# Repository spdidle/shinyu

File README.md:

# A-Side 🎼

## What is this?

A-Side is a cassette tape inspired hub to connect full size SD cards among other things to my laptop. I own several cameras but it's not convenient at all to find my dongle and connect it. So why not use a cute form to easily see your pictures!

## Why did I make this?

I love cassette tapes and cameras. That's it!

Loving cameras mean that every time I need to view my photos, upload my photos, anything to do with my photos, it's such a hassle! Grabbing my SD card reader, then my hard drive, sometimes another dongle... Anyways, it's just way too much work. So I decided to make my own SD card dongle-esque thing, with 2 USB-A ports to facilitate any connecting of hard drives, and 2 SD card slots to maximize the photo goodness. When I don't need to fiddle with photos, it can also act as a normal USB hub, allowing me to plug in keyboard or mice into my laptop.

## Features

- **2 USB-A ports** for portable hard drives, keyboards, or mice
- **2 Full-Size SD Card slots** for photos!
- **USB-C port** because nowadays, everything seems to be USB-C...

## How does it work?

Very self explanitory! Grab your favourite USB-C to USB-C cable, plug one end into your computer, the other into the hub, and voila! You are now able to plug whatever you want into this cute little cassette tape.

## Design

Designed in KiCad, schematic and board files are in this repo:

Case was designed (+ rendered) in Fusion360:

## BOM (Bill Of Materials)
|Designator                                           |Component Name / Description  |Package     |Value / Spec            |Qty|Unit Price (USD)|Total (USD)|Primary Supplier|Part Number / Source Link                                                                                                                                                                                              |
|-----------------------------------------------------|------------------------------|------------|------------------------|---|----------------|-----------|----------------|-----------------------------------------------------------------------------------------------------------------------------------------------------------------------------------------------------------------------|
|C1, C2                                               |Multilayer Ceramic Capacitor  |0805        |22pF                    |2  |0.4600          |$0.92      |LCSC            |https://www.lcsc.com/product-detail/C1804.html?s_z=n_q_CL21C220JBANNNC&lcsc_vid=FVBdVAJfRgcKUwcCQlVdBFQETlgIUlMAFFFcVAYEEVgxVlNeRlRXVVxWQVFdXzsOAxUeFF5JWBYZEEoKFBINSQcJGk4eFQsCAgIaSgADAwAHC0slQFVcU1NVTk8GEwkK       |
|C3                                                   |Multilayer Ceramic Capacitor  |0805        |1uF                     |1  |0.9400          |$0.94      |LCSC            |https://www.lcsc.com/product-detail/C28323.html?s_z=s_p_CL21B105KBFNNNE&lcsc_vid=FVBdVAJfRgcKUwcCQlVdBFQETlgIUlMAFFFcVAYEEVgxVlNeRlRXVVxQQVlbVjsOAxUeFF5JWBYZEEoKFBINSQcJGk4dAgUUFAk%3D                                |
|C10                                                  |Multilayer Ceramic Capacitor  |0805        |4.7uF                   |1  |0.4300          |$0.43      |LCSC            |https://www.lcsc.com/product-detail/C1779.html?s_z=s_p_CL21A475KAQNNNE&lcsc_vid=FVBdVAJfRgcKUwcCQlVdBFQETlgIUlMAFFFcVAYEEVgxVlNeRlRXVFVRT1lXUDsOAxUeFF5JWBYZEEoKFBINSQcJGk4dAgUUFAk%3D                                 |
|C11,C12,C13,C14,C15,C16,C17,C19,C20,C4,C5,C6,C7,C8,C9|Multilayer Ceramic Capacitor  |0805        |100nF                   |15 |0.0687          |$1.03      |LCSC            |https://www.lcsc.com/product-detail/C49678.html?s_z=n_q_CC0805KRX7R9BB104&lcsc_vid=FVBdVAJfRgcKUwcCQlVdBFQETlgIUlMAFFFcVAYEEVgxVlNeRlRXVFdQT1ZaUzsOAxUeFF5JWBYZEEoKFBINSQcJGk4eFQsCAgIaSgADAwAHC0slRlZZXkoOAwwC        |
|R1, R2, R5, R6                                       |Thick Film Chip Resistor      |0805        |100 kΩ                  |4  |0.0825          |$0.33      |LCSC            |https://www.lcsc.com/product-detail/C149504.html?s_z=s_p_0805W8F1003T5E&lcsc_vid=FVBdVAJfRgcKUwcCQlVdBFQETlgIUlMAFFFcVAYEEVgxVlNeRlRXVFFVT1deXjsOAxUeFF5JWBYZEEoKFBINSQcJGk4dAgUUFAk%3D                                |
|R4                                                   |Thick Film Chip Resistor      |0805        |680 Ω                   |1  |0.2200          |$0.22      |LCSC            |https://www.lcsc.com/product-detail/C17798.html?s_z=n_q_0805W8F6800T5E&lcsc_vid=FVBdVAJfRgcKUwcCQlVdBFQETlgIUlMAFFFcVAYEEVgxVlNeRlRXVFJVQ1BWVTsOAxUeFF5JWBYZEEoKFBINSQcJGk4eFQsCAgIaSgADAwAHC0slRlZZXlxIHxUDCw%3D%3D   |
|R7, R8                                               |Thick Film Chip Resistor      |0805        |330 Ω                   |2  |0.1400          |$0.28      |LCSC            |https://www.lcsc.com/product-detail/C17630.html?s_z=s_p_0805W8F3300T5E&lcsc_vid=FVBdVAJfRgcKUwcCQlVdBFQETlgIUlMAFFFcVAYEEVgxVlNeRlRXVFJeQlZXVjsOAxUeFF5JWBYZEEoKFBINSQcJGk4dAgUUFAk%3D                                 |
|R10, R23                                             |Thick Film Chip Resistor      |0805        |5.1 kΩ                  |2  |0.1400          |$0.28      |LCSC            |https://www.lcsc.com/product-detail/C27834.html?s_z=n_q_0805W8F5101T5E&lcsc_vid=FVBdVAJfRgcKUwcCQlVdBFQETlgIUlMAFFFcVAYEEVgxVlNeRlRXVFNXT1FeUDsOAxUeFF5JWBYZEEoKFBINSQcJGk4eFQsCAgIaSgADAwAHC0slRlZYVFRIHxUDCw%3D%3D   |
|R11-R20                                              |Thick Film Chip Resistor      |0805        |10 kΩ                   |14 |0.0250          |$0.35      |LCSC            |https://www.lcsc.com/product-detail/C17414.html?s_z=s_p_0805W8F1002T5E&lcsc_vid=FVBdVAJfRgcKUwcCQlVdBFQETlgIUlMAFFFcVAYEEVgxVlNeRlRXVFNfRFlXUjsOAxUeFF5JWBYZEEoKFBINSQcJGk4dAgUUFAk%3D                                 |
|D1, D2                                               |Surface Mount Indicator LED   |0805        |Standard Red/Green      |2  |0.3350          |$0.67      |LCSC            |https://www.lcsc.com/product-detail/C84256.html?s_z=s_p_NCD0805R1                                                                                                                                                      |
|SW1                                                  |SMT Tactile Push Button       |3.9x2.9mm   |1.6N / 2.0mm Height     |1  |2.2100          |$2.21      |LCSC            |https://www.lcsc.com/product-detail/C495942.html?s_z=n_q_MPTFP2-V-T%252FR&lcsc_vid=FVBdVAJfRgcKUwcCQlVdBFQETlgIUlMAFFFcVAYEEVgxVlNeRlRXVFxeRlRbUjsOAxUeFF5JWBYZEEoKFBINSQcJGk4eFQsCAgIaSgADAwAHC0slT1VcUlJIHxUDCw%3D%3D|
|CARD1, CARD2                                         |Hinged MicroSD Card Slot      |SMT         |SD-106M Hinged          |2  |0.5200          |$1.04      |LCSC            |https://www.lcsc.com/product-detail/C266603.html?s_z=s_p_SD-106M&lcsc_vid=FVBdVAJfRgcKUwcCQlVdBFQETlgIUlMAFFFcVAYEEVgxVlNeRlRXVF1VQFZXVDsOAxUeFF5JWBYZEEoKFBINSQcJGk4dAgUUFAk%3D                                       |
|GL850G                                               |USB 2.0 Hub Controller IC     |SSOP-28     |GL850G-HHY22            |1  |0.5500          |$0.55      |LCSC            |https://www.lcsc.com/product-detail/C136617.html?s_z=n_q_GL850G-HHY22&lcsc_vid=FVBdVAJfRgcKUwcCQlVdBFQETlgIUlMAFFFcVAYEEVgxVlNeRlRXVF1eTllbXzsOAxUeFF5JWBYZEEoKFBINSQcJGk4eFQsCAgIaSgADAwAHC0slRVdYUVRVWQkaCgg%3D      |
|IC3, IC4                                             |USB SD Card Reader Controller |SOP-16      |GL823K-HCY04            |2  |0.4550          |$0.91      |LCSC            |https://www.lcsc.com/product-detail/C284879.html?s_z=n_q_GL823K-HCY04&lcsc_vid=FVBdVAJfRgcKUwcCQlVdBFQETlgIUlMAFFFcVAYEEVgxVlNeRlRXU1RSR1JZVzsOAxUeFF5JWBYZEEoKFBINSQcJGk4NBhADEA4cHktfQ1hADxALGw%3D%3D                |
|U1, U2                                               |TVS Diode ESD Protection Array|SOT-23-6    |SRV05-4 (Low Cap)       |2  |0.2550          |$0.51      |LCSC            |https://www.lcsc.com/product-detail/C2836319.html?s_z=n_q_x_SRV05-4&lcsc_vid=FVBdVAJfRgcKUwcCQlVdBFQETlgIUlMAFFFcVAYEEVgxVlNeRlRXU1RRRFlfVTsOAxUeFF5JWBYZEEoKFBINSQcJGk4NBhADEA4cHktfQ1hADxALGw%3D%3D                  |
|USB1, USB2                                           |USB Type-A Receptacle         |Through-Hole|Right Angle / 90° Female|2  |0.2450          |$0.49      |LCSC            |https://www.lcsc.com/product-detail/C456018.html?s_z=n_q_p_AF%252090%2520WJDG&lcsc_vid=FVBdVAJfRgcKUwcCQlVdBFQETlgIUlMAFFFcVAYEEVgxVlNeRlRXU1VURlNYUDsOAxUeFF5JWBYZEEoKFBINSQcJGk4eFQsCAgIaSgADAwAHC0slRVldUVdXTk8GEwkK|
|USB3                                                 |USB Type-C Receptacle         |SMT+TH      |16-Pin 2MD Type-C       |1  |1.4100          |$1.41      |LCSC            |https://www.lcsc.com/product-detail/C2765186.html?s_z=n_q_TYPE-C%252016PIN%25202MD(073)&lcsc_vid=FVBdVAJfRgcKUwcCQlVdBFQETlgIUlMAFFFcVAYEEVgxVlNeRlRXU1VQRFZaUDsOAxUeFF5JWBYZEEoKFBINSQcJGk4dAgUUFAk%3D                |
|Y2                                                   |Quartz Resonator Crystal      |3225 SMT    |26.2982 MHz / 4-Pad     |1  |0.1400          |$0.14      |LCSC            |https://www.lcsc.com/product-detail/C2981681.html?s_z=n_q_3225-26.2982-22-10-10%252FA                                                                                                                                  |
|PCB                                                  |Custom 2-Layer Circuit Board  |100x80mm    |FR-4 / 1.6mm Thickness  |5  |0.7000          |$3.50      |JLCPCB          |https://www.jlcpcb.com                                                                                                                                                                                                 |
|                                                     |                              |            |                        |   |                |           |                |                                                                                                                                                                                                                       |
|                                                     |                              |            |                        |   |                |$16.21     |                |                                                                                                                                                                                                                       |

## Build & Assembly
(I may or may not be larping, I've never soldered anything this miniscule before so bare with me and my limited theory knowledge)

### Required Tools
- Soldering iron
- Solder
- Tweezers
- Tacky Flux
- IPA & ESD Brush

### Assmebly  Steps

#### Solder on the microchips (the lowest profile ones), which include the GL850G, GL823K, and the ESD Protection Diodes.
1. Apply a thin layer of tacky flux to the PCB pads
2. Align and place the chip
3. Tack down one corner pin with a tiny dab of solder
4. Apply flux across all pins, and solder everything together

#### Solder on any passives, including resistors, caps, crystals, and LEDs
1. Use the two-pad SMT technique, applying a small dab of solder on one pad
2. Slide the component into the solder using tweezers
3. Solder the remaining pad

#### Solder on the electromechanical components, which include the tactile switch and SD card slots
1. Just do it? Haha?

#### Solder on the final, highest profile components, including the USB IO connectors
1. Put the connector into the holes on the PCB, and solder from the bottom
2. Use a magnifying glass for the USB-C, the 16 pins are going to be hell.

#### If you can afford PCBA, good for you. Ignore everything I just said >:(

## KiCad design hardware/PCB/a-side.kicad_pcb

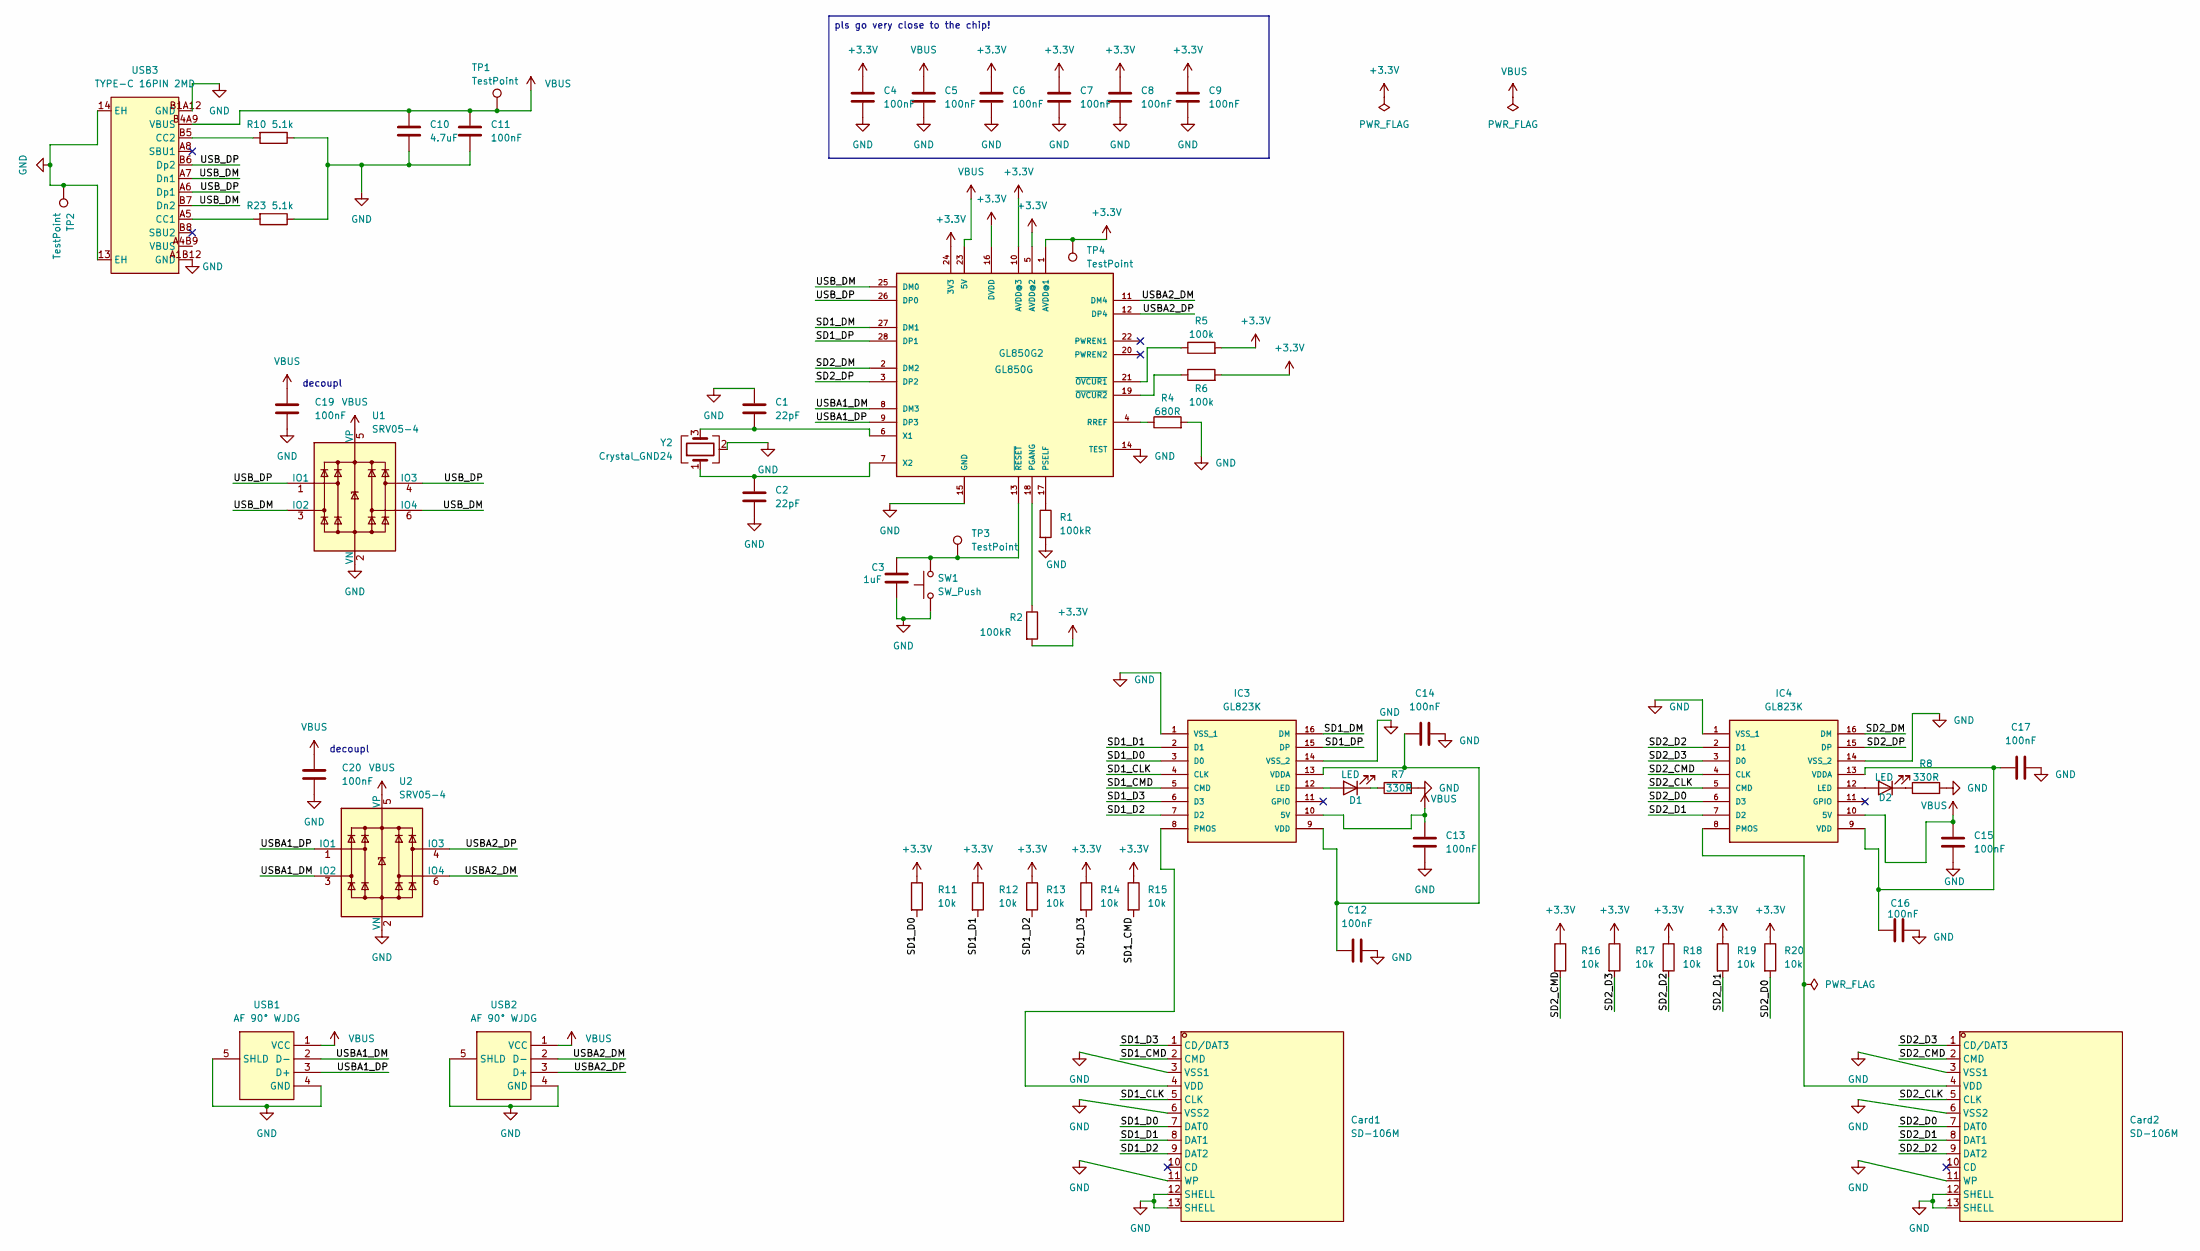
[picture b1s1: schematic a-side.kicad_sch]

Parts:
C1, C2: 22pF; C_0805_2012Metric
C3: 1uF; C_0805_2012Metric
C4, C5, C6, C7, C8, C9, C11, C12, C13, C14, C15, C16, C17, C19, C20: 100nF; C_0805_2012Metric
C10: 4.7uF; C_0805_2012Metric
Card1, Card2: SD-106M; SD-SMD_SD-106M; MPN SD-106M; LCSC Part C266603
D1, D2: LED; LED_0805_2012Metric_Pad1.15x1.40mm_HandSolder
GL850G2: GL850G; 28SSOP
IC3, IC4: GL823K; SOP64P600X175-16N; MANUFACTURER_PART_NUMBER GL823K
R1, R2: 100kR; R_0805_2012Metric
R4: 680R; R_0805_2012Metric
R5, R6: 100k; R_0805_2012Metric
R7, R8: 330R; R_0805_2012Metric
R10, R23: 5.1k; R_0805_2012Metric
R11, R12, R13, R14, R15, R16, R17, R18, R19, R20: 10k; R_0805_2012Metric
SW1: SW_Push; SW_Push_SPST_NO_Alps_SKRK
TP1, TP2, TP3, TP4: TestPoint; TestPoint_Pad_D1.0mm
U1, U2: SRV05-4; SOT-23-6
USB1, USB2: AF 90° WJDG; USB-A-TH_AF-WJDG; MPN AF 90° WJDG; LCSC Part C456018
USB3: TYPE-C 16PIN 2MD; USB-C-SMD_TYPE-C-16PIN-2MD-073; MPN TYPE-C 16PIN 2MD(073); LCSC Part C2765186
Y2: Crystal_GND24; Crystal_SMD_3225-4Pin_3.2x2.5mm

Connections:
+3.3V: C4.1, C6.1, C7.1, C8.1, C9.1, GL850G2.1 (AVDD@1), GL850G2.5 (AVDD@2), GL850G2.10 (AVDD@3), GL850G2.16 (DVDD), GL850G2.24 (3V3), R2.2, R5.2, R6.2, R11.1, R12.1, R13.1, R14.1, R15.1, R16.1, R17.1, R18.1, R19.1, R20.1, TP4.1 (1_1)
/SD1_CLK: Card1.5 (CLK), IC3.4 (CLK)
/SD1_CMD: Card1.2 (CMD), IC3.5 (CMD), R15.2
/SD1_D0: Card1.7 (DAT0), IC3.3 (D0), R11.2
/SD1_D1: Card1.8 (DAT1), IC3.2 (D1), R12.2
/SD1_D2: Card1.9 (DAT2), IC3.7 (D2), R13.2
/SD1_D3: Card1.1 (CD/DAT3), IC3.6 (D3), R14.2
/SD1_DM: GL850G2.27 (DM1), IC3.16 (DM)
/SD1_DP: GL850G2.28 (DP1), IC3.15 (DP)
/SD2_CLK: Card2.5 (CLK), IC4.5 (CMD)
/SD2_CMD: Card2.2 (CMD), IC4.4 (CLK), R16.2
/SD2_D0: Card2.7 (DAT0), IC4.6 (D3), R20.2
/SD2_D1: Card2.8 (DAT1), IC4.7 (D2), R19.2
/SD2_D2: Card2.9 (DAT2), IC4.2 (D1), R18.2
/SD2_D3: Card2.1 (CD/DAT3), IC4.3 (D0), R17.2
/SD2_DM: GL850G2.2 (DM2), IC4.16 (DM)
/SD2_DP: GL850G2.3 (DP2), IC4.15 (DP)
/USBA1_DM: GL850G2.8 (DM3), U2.3 (IO2), USB1.2 (D-)
/USBA1_DP: GL850G2.9 (DP3), U2.1 (IO1), USB1.3 (D+)
/USBA2_DM: GL850G2.11 (DM4), U2.6 (IO4), USB2.2 (D-)
/USBA2_DP: GL850G2.12 (DP4), U2.4 (IO3), USB2.3 (D+)
/USB_DM: GL850G2.25 (DM0), U1.3 (IO2), U1.6 (IO4), USB3.A7 (Dn1), USB3.B7 (Dn2)
/USB_DP: GL850G2.26 (DP0), U1.1 (IO1), U1.4 (IO3), USB3.A6 (Dp1), USB3.B6 (Dp2)
GND: C1.1, C2.2, C3.1, C4.2, C5.2, C6.2, C7.2, C8.2, C9.2, C10.1, C11.2, C12.2, C13.2, C14.2, C15.2, C16.2, C17.2, C19.2, C20.2, Card1.3 (VSS1), Card1.6 (VSS2), Card1.11 (WP), Card1.12 (SHELL), Card1.13 (SHELL), Card2.3 (VSS1), Card2.6 (VSS2), Card2.11 (WP), Card2.12 (SHELL), Card2.13 (SHELL), GL850G2.14 (TEST), GL850G2.15 (GND), IC3.1 (VSS_1), IC3.14 (VSS_2), IC4.1 (VSS_1), IC4.14 (VSS_2), R1.2, R4.2, R7.2, R8.2, R10.1, R23.1, SW1.1, TP2.1 (1_1), U1.2 (VN), U2.2 (VN), USB1.4 (GND), USB1.5 (SHLD), USB2.4 (GND), USB2.5 (SHLD), USB3.13 (EH), USB3.14 (EH), USB3.A1B12 (GND), USB3.B1A12 (GND), Y2.2 (G), Y2.4 (G)
unnamed: Card1.4 (VDD), IC3.8 (PMOS)
unnamed: Card2.4 (VDD), IC4.8 (PMOS)
unnamed: D1.2 (A), IC3.12 (LED)
unnamed: D1.1 (K), R7.1
unnamed: D2.2 (A), IC4.12 (LED)
unnamed: D2.1 (K), R8.1
unnamed: GL850G2.18 (PGANG), R2.1
unnamed: GL850G2.17 (PSELF), R1.1
unnamed: GL850G2.4 (RREF), R4.1
unnamed: C1.2, GL850G2.6 (X1), Y2.3
unnamed: C2.1, GL850G2.7 (X2), Y2.1
unnamed: GL850G2.21 (~OVCUR1), R5.1
unnamed: GL850G2.19 (~OVCUR2), R6.1
unnamed: C3.2, GL850G2.13 (~RESET), SW1.2, TP3.1 (1_1)
unnamed: C12.1, C14.1, IC3.9 (VDD), IC3.13 (VDDA)
unnamed: C16.1, C17.1, IC4.9 (VDD), IC4.13 (VDDA)
unnamed: R23.2, USB3.A5 (CC1)
unnamed: R10.2, USB3.B5 (CC2)
VBUS: C5.1, C10.2, C11.1, C13.1, C15.1, C19.1, C20.1, GL850G2.23 (5V), IC3.10 (5V), IC4.10 (5V), TP1.1 (1_1), U1.5 (VP), U2.5 (VP), USB1.1 (VCC), USB2.1 (VCC), USB3.B4A9 (VBUS)

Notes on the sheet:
decoupl
pls go very close to the chip!

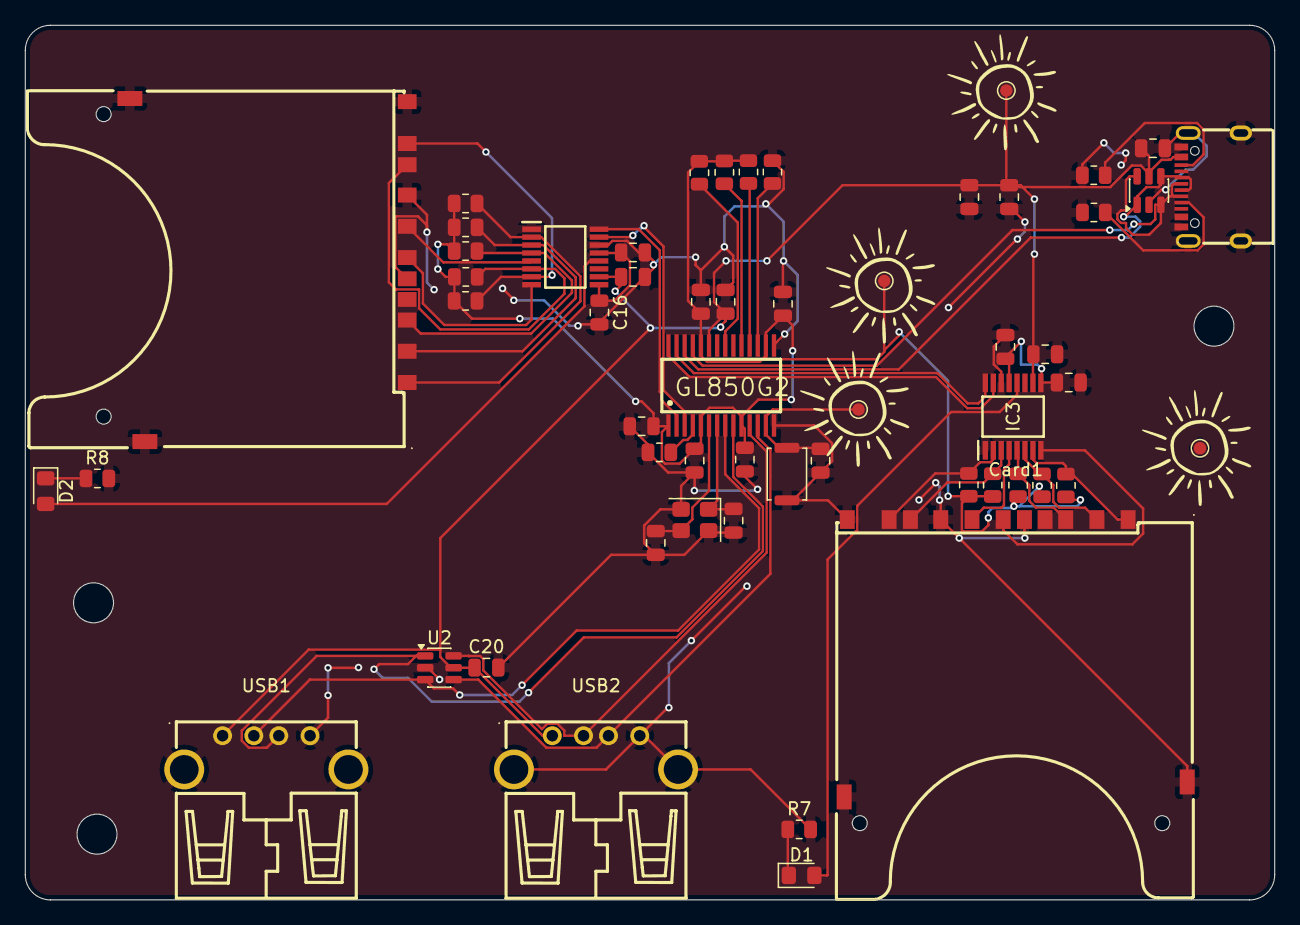
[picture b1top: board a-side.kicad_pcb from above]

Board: 2 copper layers, 100.0 x 70.0 mm, 56 parts (0 on the bottom side), 43 nets.

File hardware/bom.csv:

Designator,Component Name / Description,Package,Value / Spec,Qty,Unit Price (USD),Total (USD),Primary Supplier,Part Number / Source Link
"C1, C2",Multilayer Ceramic Capacitor,0805,22pF,2,0.4600,$0.92,LCSC,https://www.lcsc.com/product-detail/C1804.html?s_z=n_q_CL21C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
C3,Multilayer Ceramic Capacitor,0805,1uF,1,0.9400,$0.94,LCSC,https://www.lcsc.com/product-detail/C28323.html?s_z=s_p_CL21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
C10,Multilayer Ceramic Capacitor,0805,4.7uF,1,0.4300,$0.43,LCSC,https://www.lcsc.com/product-detail/C1779.html?s_z=s_p_CL21A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
"C11,C12,C13,C14,C15,C16,C17,C19,C20,C4,C5,C6,C7,C8,C9",Multilayer Ceramic Capacitor,0805,100nF,15,0.0687,$1.03,LCSC,https://www.lcsc.com/product-detail/C49678.html?s_z=n_q_CC08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
"R1, R2, R5, R6",Thick Film Chip Resistor,0805,100 kΩ,4,0.0825,$0.33,LCSC,https://www.lcsc.com/product-detail/C149504.html?s_z=s_p_080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
R4,Thick Film Chip Resistor,0805,680 Ω,1,0.2200,$0.22,LCSC,https://www.lcsc.com/product-detail/C17798.html?s_z=n_q_0805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
"R7, R8",Thick Film Chip Resistor,0805,330 Ω,2,0.1400,$0.28,LCSC,https://www.lcsc.com/product-detail/C17630.html?s_z=s_p_0805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
"R10, R23",Thick Film Chip Resistor,0805,5.1 kΩ,2,0.1400,$0.28,LCSC,https://www.lcsc.com/product-detail/C27834.html?s_z=n_q_0805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
R11-R20,Thick Film Chip Resistor,0805,10 kΩ,14,0.0250,$0.35,LCSC,https://www.lcsc.com/product-detail/C17414.html?s_z=s_p_0805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
"D1, D2",Surface Mount Indicator LED,0805,Standard Red/Green,2,0.3350,$0.67,LCSC,https://www.lcsc.com/product-detail/C84256.html?s_z=s_p_NCD0805R1
SW1,SMT Tactile Push Button,3.9x2.9mm,1.6N / 2.0mm Height,1,2.2100,$2.21,LCSC,https://www.lcsc.com/product-detail/C495942.html?s_z=n_q_MPT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
"CARD1, CARD2",Hinged MicroSD Card Slot,SMT,SD-106M Hinged,2,0.5200,$1.04,LCSC,https://www.lcsc.com/product-detail/C266603.html?s_z=s_p_SD-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
GL850G,USB 2.0 Hub Controller IC,SSOP-28,GL850G-HHY22,1,0.5500,$0.55,LCSC,https://www.lcsc.com/product-detail/C136617.html?s_z=n_q_GL8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
"IC3, IC4",USB SD Card Reader Controller,SOP-16,GL823K-HCY04,2,0.4550,$0.91,LCSC,https://www.lcsc.com/product-detail/C284879.html?s_z=n_q_GL8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
"U1, U2",TVS Diode ESD Protection Array,SOT-23-6,SRV05-4 (Low Cap),2,0.2550,$0.51,LCSC,https://www.lcsc.com/product-detail/C2836319.html?s_z=n_q_x_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
"USB1, USB2",USB Type-A Receptacle,Through-Hole,Right Angle / 90° Female,2,0.2450,$0.49,LCSC,https://www.lcsc.com/product-detail/C456018.html?s_z=n_q_p_A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
USB3,USB Type-C Receptacle,SMT+TH,16-Pin 2MD Type-C,1,1.4100,$1.41,LCSC,https://www.lcsc.com/product-detail/C2765186.html?s_z=n_q_TY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
Y2,Quartz Resonator Crystal,3225 SMT,26.2982 MHz / 4-Pad,1,0.1400,$0.14,LCSC,https://www.lcsc.com/product-detail/C2981681.html?s_z=n_q_32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
PCB,Custom 2-Layer Circuit Board,100x80mm,FR-4 / 1.6mm Thickness,5,0.7000,$3.50,JLCPCB,https://www.jlcpcb.com
,,,,,,,,
,,,,,,$16.21,,

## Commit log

2026-04-06 last com 4 tonight
    kicking ts bucket. finished tracing with 0 errors and opened my 3d viewer to see i had the wrong footprint for my usb c plug 🥰 that no its actuallyt amazing! its exactly what i wanted! so im restarti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
2026-04-12 okay. i give up.
    fine lapse you win. i lost all a nights work! you are the besttt! thank you! also changed the name because i crashed out so hard today that i changed the entire direction of the project. fun times.
2026-04-13 ???? short ahh
    cant sleep so decided to do a 5 min work sesh , added 2 leds for the sd card readers ohh my god chat i literally cant fall asleep its 4 am 😭
2026-04-15 last commie of the day!
    fixed major issues earlier, rn just fixing some decoupling caps here and there heh i mean all in a days work what can i say
2026-04-18 fixing..
    schematic... fixing orientation on stuffs... fixing footprints again... fixing...
2026-06-14 getting deep into routing
    just gonna commit rn coz im a little locked in but uhh yea schema done i think, footprints all found
2026-06-14 DOME
    done done done DONE 0 errors 108982 warnings who gaf im done
2026-06-14 im actually moronic
    how did i forget mounting holes. and also. THEY DONT FIT IN THE 4 CORNERS should i just die
2026-06-14 import, export blahhh
    get the case done and exporting some final stuff iwth pcb and case
2026-06-15 shuffling files around
    dont mind me
2026-06-15 stupid pcb still says g
    made a mistaje on silkscreen, redid the exporrts and pcb.step file
2026-06-15 blahhhh readmetime
2026-06-15 Revise README
2026-06-16 update readme
    update readme with new assembly/solder instructions and bom
2026-06-16 polish
    + gitignore
    + reorganize files
    + add bom to hardware folder
    + delete unnecessary clutter
2026-06-16 Reset Git cache and apply new .gitignore rules
2026-06-16 apply gitignore rules and purge hardware backups
2026-06-16 added step files
    i dont thnnk i need this but just in CASE HAHAHAHAHAHA GET IT JUST IN CASE AS IN THE 3D CASE
